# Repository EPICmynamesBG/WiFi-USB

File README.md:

# WiFi-USB #
A wirelessly controllable USB power port

_Firmware Version:_ 2.0

_iOS App Version_: 0.4

_Web App Version_: 0.3

---

## About ##

_What is WiFi-USB?_

WiFi-USB is an IoT device and software that enables a USB powered device (up to 2.0 A) to be remotely powered on and off.

_Why WiFi-USB?_

The inspiration for this project came from a general irritation with a USB powered device that did not have an inline power switch. Wall outlets aren't always in the most convenient of places, so plugging/unplugging this USB port from a wall adapter all the time could be a hassle.

_How can I use WiFi-USB?_

Keep reading below for more on how to build your own WiFi-USB board, and instructions on how to install the firmware to get your device up and running.

## Examples/Usage ##

## Important Notes ##

** Never plug both the mini-USB power supply and the FTDI power at the same time. The hardware is not designed to handle this and will surely break **

## Recent Updates ##

### Web v0.3 ###

- Who needs jQuery? Not us!
- Web Sockets = live data!

### Firmware v2.0 ###

- Web Socket connections are now possible, keeping all clients in sync

### Firmware v1.2 ###

- Introducing Access Point Broadcasting fallback when client connect mode fails

## Hardware ##

Files and instructions will be posted soon.

## Firmware Install ##

1. Download and install the [Arduino IDE](https://www.arduino.cc/en/Main/Software)
2. Configure the IDE using the instructions [here](https://github.com/esp8266/arduino#installing-with-boards-manager)
3. In the Arduino IDE, go to Sketch > Include Library > Manage Libraries. Search 'WebSockets', and install the latest version of WebSockets by Marcus Sattler [GitHub](https://github.com/Links2004/arduinoWebSockets)
4. Download the zip/clone this repo
5. In `config.h` update the SSID and SSID_PASSWORD variables to match your network configuration.
6. Open `firmware.ino` and click upload in the Arduino IDE when the device is in develop mode

## Web Install ##

The appropriate web files are already in the WiFi-USB's firmware > data folder. Simply follow [this guide](https://github.com/esp8266/arduino-esp8266fs-plugin) on how to install and upload the those files to WiFi-USB for the web control panel to become available.

## Installing the iOS & Watch app (Requires a Mac) ##

1. Install [XCode](https://itunes.apple.com/us/app/xcode/id497799835?mt=12) on your system
  - Built using XCode 7.3.1
2. Open  WiFi-USB.xcodeproj
3. Select the Project (the blue icon) from the Nvigation bar
  - Under Targets, change the team on each one to the team of your desire (probably personal or None)
4. Now plug in your device, and click the Play arrow to Run the app on your device
  - If you have a watch, to install the watch app, on the bar next to the run button, select WK-WiFi-USB as your build target, then selecte your device with watch, and hit Run 

## Using WiFi-USB ##

The default endpoint for WiFi-USB will be [http://wifiusb.local](http://wifiusb.local). Going to this page will show you a simple html page, confirming that the wifiusb is running.

WiFi-USB is configured with 3 REST endpoints that will return JSON data:

_Check the status of the USB's power_
* `/status` - GET (no parameters)
  * `on: Bool` - simple check if USB is on or off
  * `raw: Int` - the raw GPIO pin value for the USB pin 
  * `description: String` - a textual description of the USB power status

_Toggle the USB power on/off_
* `/toggle` - POST (no parameters)
  * `on: Bool` - simple check if USB is on or off
  * `raw: Int` - the raw GPIO pin value for the USB pin 
  * `description: String` - a textual description of the USB power status

_Reboot the device_
* `/reboot` - GET (no parameters)
  * `description: String` - a textual confirmation that the device is rebooting

## Future Ideas ##
* Add a timer/alarm clock ability. Turn on/off at a set time!
* ~~Create an Apple Watch extensnion ~~
* Add WebSocket ability for live status sync across all controller devices

## Credits ##

[Alex Cordonnier](https://github.com/ajcord) - for designing the board and helping me troubleshoot every step of the way!

## Licenses ##

[_firmware_](https://github.com/EPICmynamesBG/WiFi-USB/blob/master/firmware/LICENSE) : GNU GPLv3

[_iOS_](https://github.com/EPICmynamesBG/WiFi-USB/blob/master/iOS/LICENSE) : GNU GPLv3

[_iOS_](https://github.com/EPICmynamesBG/WiFi-USB/blob/master/web/LICENSE) : GNU GPLv3

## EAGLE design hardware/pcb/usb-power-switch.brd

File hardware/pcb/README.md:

# WiFi-USB PCB v3

This folder contains the Eagle CAD files for the WiFi-USB circuit board.

To install Eagle with a free Express or Educational license, go to
https://cadsoft.io.

It also contains a PDF of the schematic and an image of the board layout
if you want to view the design without installing Eagle.

## Parts

These saved cart links include all the parts necessary to build one board.

* DigiKey: http://www.digikey.com/short/3mnpbh
* Mouser: http://www.mouser.com/ProjectManager/ProjectDetail.aspx?AccessID=066B4F095A
* Sparkfun: https://www.sparkfun.com/products/9717
    - This cable is reusable for many other kinds of projects.
      It is possible to use an alternative to avoid buying an expensive new
      cable, as long as the Tx and Rx signals are 3.3V. The ESP8266 may get
      fried by 5V signals. However, Vcc goes through the voltage regulator and
      is therefore 5V tolerant.

## Fabrication

I recommend ordering PCBs through [OSH Park](https://oshpark.com).
It only costs about $11 for 3 copies of this board, the quality is good,
and they come in a very regal purple and gold.
There are of course many other options you may prefer, but for newcomers,
OSH Park is recommended.

## Building

TODO (Brandon): add build instructions/hints

## Mounting

The mounting holes on the PCB are 2.79mm in diameter, designed to fit
M2.5 screws. These mounting holes are not grounded in the interest of
saving board space.

## Changelog (v3):
* Redesigned form factor to be longer and thinner with receptacles on
  opposite sides
* Added mounting holes
* Removed USB data connection &mdash; only passes through power now
* Grounded USB receptacle chassis
* Added pads around USB-A mounting holes and voltage regulator heatsink
* Eliminated some unnecessary resistors
* Added OSHW logo

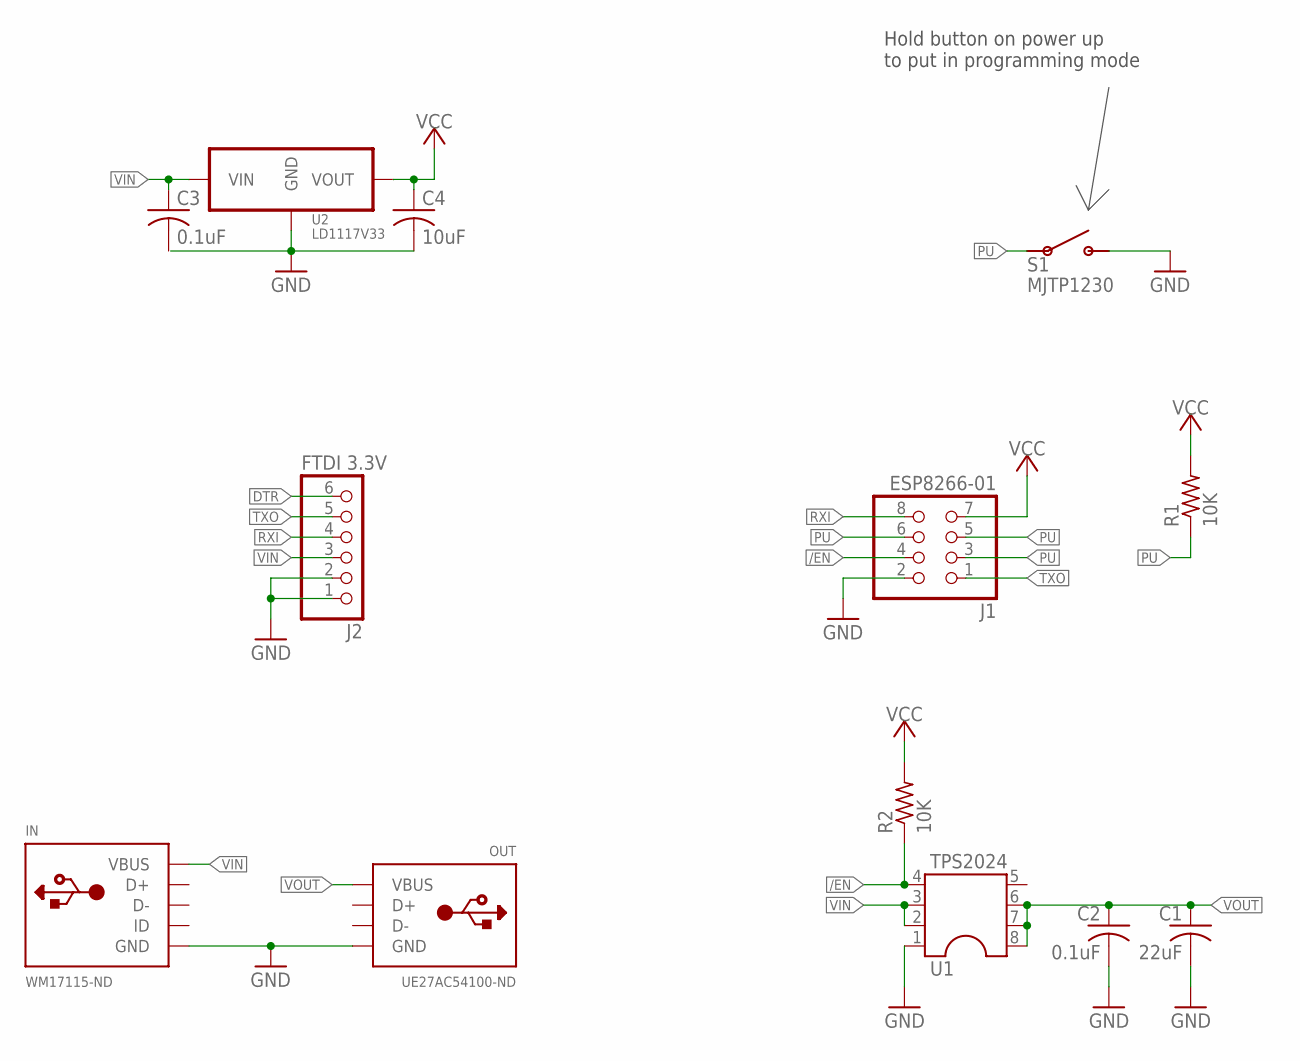
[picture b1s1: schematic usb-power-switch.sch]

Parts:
C1: 22uF; C025-025X050
C2, C3: 0.1uF; C025-025X050
C4: 10uF; C025-025X050
IN: WM17115-ND; USB-MINI-B
J1: ESP8266-01; 2X04
J2: FTDI 3.3V; 1X06
OUT: UE27AC54100-ND; USB-A
R1, R2: 10K; 0207/10
S1: MJTP1230; TACTILE-BUTTON-MJTP1230
U1: TPS2024; DIL08
U2: LD1117V33; TO-220

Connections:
/EN: J1.4, R2.1, U1.4
DTR: J2.6
GND: C1.2, C2.2, C4.2, IN.GND, IN.GND1 (GND), IN.GND4 (GND), J1.2, J2.1, J2.2, OUT.P$4 (GND), OUT.P$5 (GND), OUT.P$6 (GND), S1.P$2 (3), S1.P$4 (3), U1.1, U2.P$1 (GND)
PU: J1.3, J1.5, J1.6, R1.1, S1.P$1 (1), S1.P$3 (1)
RXI: J1.8, J2.4
TXO: J1.1, J2.5
VCC: C4.1, J1.7, R1.2, R2.2, U2.P$2 (VOUT), U2.P$4 (VOUT)
VIN: C3.1, IN.VBUS, J2.3, U1.2, U1.3, U2.P$3 (VIN)
VOUT: C1.1, C2.1, OUT.P$1 (VBUS), U1.6, U1.7, U1.8

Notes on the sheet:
Hold button on power up to put in programming mode

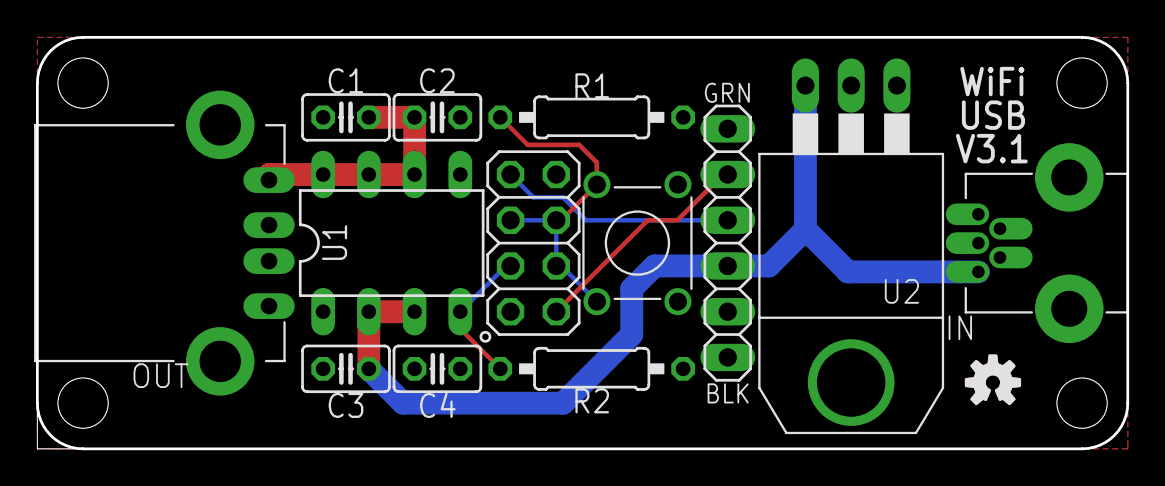
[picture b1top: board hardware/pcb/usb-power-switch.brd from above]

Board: 2 copper layers, 60.6 x 22.9 mm, 15 parts (0 on the bottom side), 8 nets.

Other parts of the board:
U$1: OSHW-LOGO-S
U$2: OSHW-LOGO-S_COPPER

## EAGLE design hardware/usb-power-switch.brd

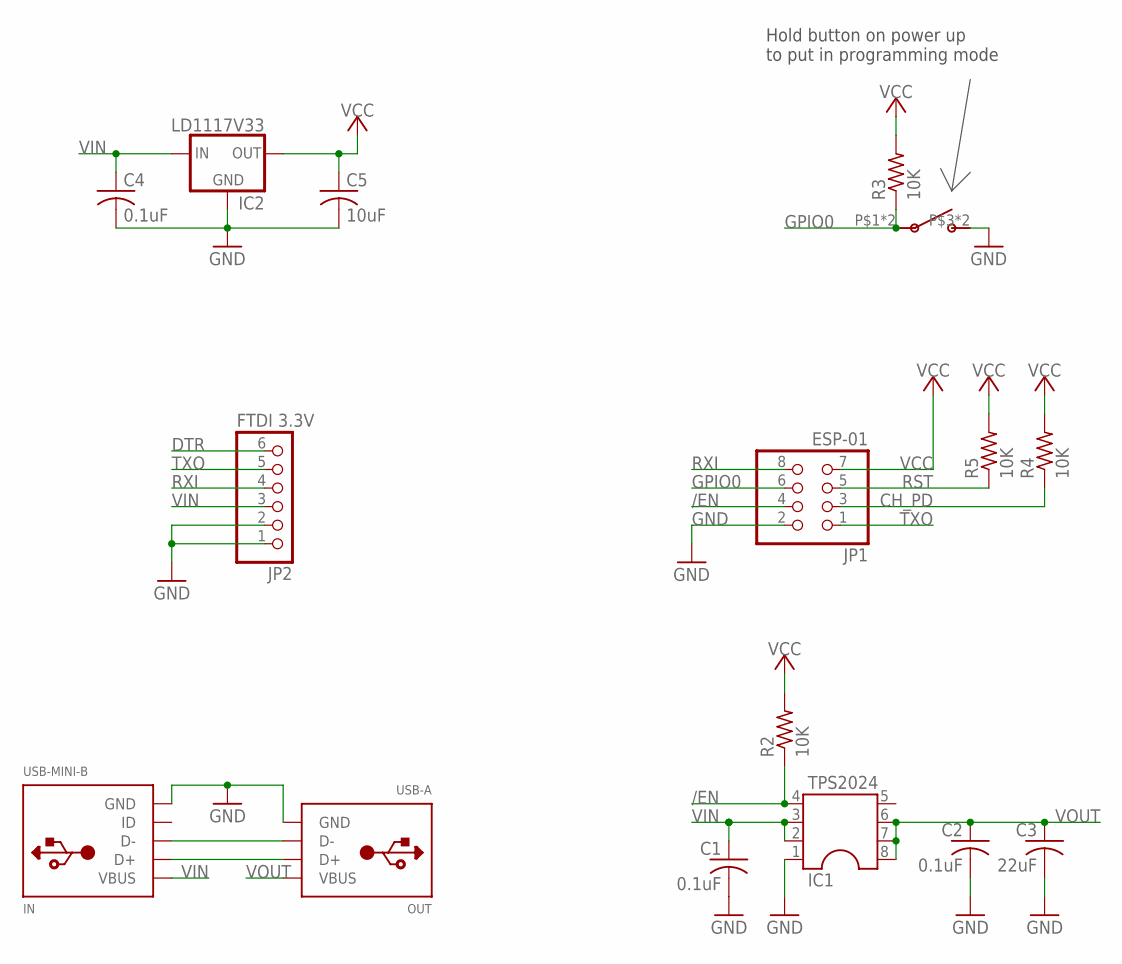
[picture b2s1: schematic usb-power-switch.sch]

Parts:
C1, C2, C4: 0.1uF; C025-025X050
C3: 22uF; C025-025X050
C5: 10uF; C025-025X050
IC1: TPS2024; DIL08
IC2: LD1117V33; 78XXL
IN: USB-MINI-B
JP1: ESP-01; 2X04
JP2: FTDI 3.3V; 1X06
OUT: USB-A
R2, R3, R4, R5: 10K; 0204/7
S1: TACTILE-BUTTON-MJTP1230

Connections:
/EN: IC1.4, JP1.4, R2.1
CH_PD: JP1.3, R4.1
D+: IN.D+, OUT.P$3 (D+)
D-: IN.D-, OUT.P$2 (D-)
DTR: JP2.6
GND: C1.2, C2.2, C3.2, C4.2, C5.2, IC1.1, IC2.IN (GND), IN.GND, JP1.2, JP2.1, JP2.2, OUT.P$4 (GND), S1.P$3 (3), S1.P$4 (3)
GPIO0: JP1.6, R3.1, S1.P$1 (1), S1.P$2 (1)
RST: JP1.5, R5.1
RXI: JP1.8, JP2.4
TXO: JP1.1, JP2.5
VCC: C5.1, IC2.GND (OUT), JP1.7, R2.2, R3.2, R4.2, R5.2
VIN: C1.1, C4.1, IC1.2, IC1.3, IC2.OUT (IN), IN.VBUS, JP2.3
VOUT: C2.1, C3.1, IC1.6, IC1.7, IC1.8, OUT.P$1 (VBUS)

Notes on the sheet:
Hold button on power up to put in programming mode

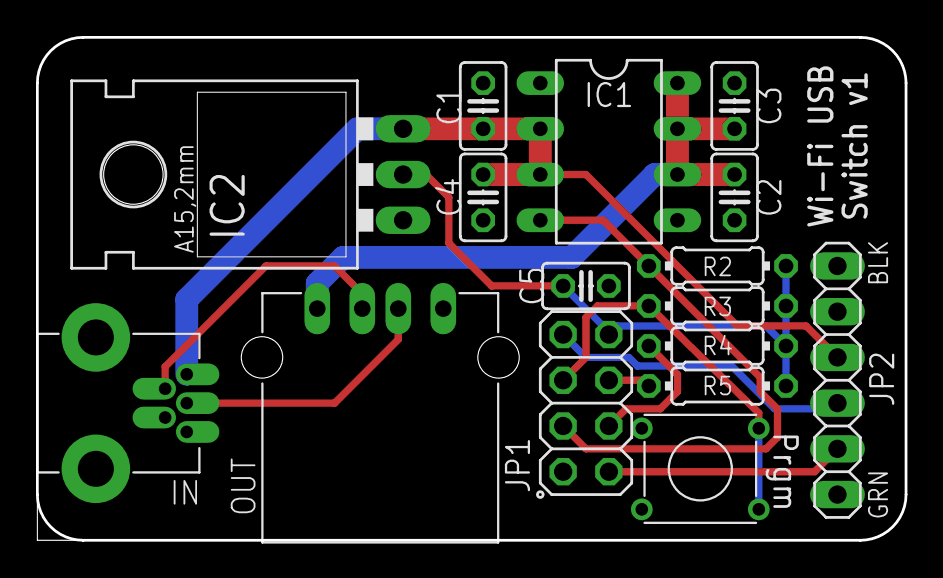
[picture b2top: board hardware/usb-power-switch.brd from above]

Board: 2 copper layers, 48.3 x 27.9 mm, 16 parts (0 on the bottom side), 12 nets.

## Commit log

2016-06-23 Bug/syntax/spelling fixes. Working product!
2016-06-23 Make Version 1
2016-06-23 Simplify functions by using isOn() more
2016-06-23 Spell fix
2016-06-23 Code cleanup
2016-06-23 add hardware files - needs updated to latest version
2016-06-23 Add copyright information
2016-06-23 Fixed several layout issues and removed unnecessary capacitor
2016-06-23 Add gitignore for Eagle
2016-06-24 Create LICENSE
2016-06-24 Add License comment to header
2016-06-24 Reorg file structure
2016-06-24 Create dev branch
2016-06-24 Update comment on LICENSE location
2016-06-24 XCode proj setup, create ColorPalette, enable color fading view background, update info.plist with HTTP site exception
2016-06-24 Create Networker and JsonResponse struct
2016-06-24 Connect WiFiUSBNetworker to VC for testing
2016-06-25 Update background rainbow effect, custom PowerButton with animations
2016-06-26 Create InfoView contained within Main VC
2016-06-26 Updated image, set power icon as template to enable masking
2016-06-26 Custom UI object creation, replace PowerButton with Glowing Button and Gradient Button
2016-06-26 Remove WiFiUSBStatus. Update Networker to better handle offline and reboot
2016-06-26 Update Main VC, now with container view, toast messages, and better display/network response handling
2016-06-26 Relocated project on machine to stop unknown prelaunch crash
2016-06-26 Update glow colors, update networker to handle no network connection case better
2016-06-26 Implement network timeouts, subtle UI changes, handle offline better, slide in/out notification animation
2016-06-26 Update LISCENSE and header comments
2016-06-26 Add LICENSE, code cleaning/documenting
2016-06-26 Update version, add app close/resume support. Stops/starts animations, refeshes power status
2016-06-27 Skeleton, background animation, reboot button with animation, power button with animation
2016-06-29 Image reorg, finish html and css, including responsive css
2016-06-29 Updated icon and logo
2016-06-29 Fix power button click, base JS functionality
2016-06-30 Unnofficial v0.1. Full functionality. Fixed some styling, added toast messages, network requests work. Small bug left on the toast, and no handling for while rebooting.
2016-07-03 Remove outdated hardware info
2016-07-03 Minor edits
2016-07-03 Actually calculated the max current
    The TPS2024 has a maximum recommended current of 2A. The power traces are 50 mil, so assuming 1oz copper, 2A would cause a 23ºC temperature rise. At room temperature, that would heat the traces to ar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
2016-07-06 Revert to remote jquery cdn, let -> var, minified versions
2016-07-06 minified pngs
2016-07-06 add site data
2016-07-07 Host web controller
2016-07-07 Move image files
2016-07-07 Web app metas, fix toast overscroll bug, fix iOS Safari body scroll issue
2016-07-07 Update hosted files, adjust serveStatic appropriately, update version header
2016-07-07 Resolve issue of app not running on physical device
2016-07-07 Create WatchKit extenstion/app and glance. Updated necessary Model files to suppoer Watch use. Complication pending
2016-07-10 Strip WK to just app only
2016-07-10 Update README, prepare for release
2016-07-11 Update README, add web license
2016-07-18 Change reload watch icon
2016-07-18 Add example images
2016-07-18 Update images
2016-07-18 Shrink images
2016-07-18 Add examples/images to README
2016-07-30 Add Access Point fallback
2016-07-30 BROKEN - Adding SocketServer capability. Client currently can connect, causing server to crash.
2016-07-31 Successfully implement Websocket connection
2016-07-31 Updated support for WebSockets, strip out jquery
2016-07-31 Actually remove all jQuery
2016-07-31 Adjust status to only reply to sender
2016-07-31 remove custom font to prevent load delays
2016-07-31 Update versioning
2016-07-31 Adding WebSocket support
2016-08-14 Added PCB design
2016-08-15 Updated PCB to v3
2016-08-16 Optimized routing, added repo URL

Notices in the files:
parts and their libraries:
SparkFun-Aesthetics: Licensing: Creative Commons ShareAlike 4.0 International - https://creativecommons.org/licenses/by-sa/4.0
